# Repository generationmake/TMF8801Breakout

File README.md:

# TMF8801Breakout
Breakout board for the ams TMF8801 1D time-of-flight sensor

## Pinout

### CN1 and CN2

This is a regular 0.1-inch pin header.

| pin number | signal on CN1 | signal on CN2|
|:----------:|:-------------:|:------------:|
| 1          | VCC           | VCC          |
| 2          | GND           | GND          |
| 3          | I2C_SDA       | I2C_SDA      |
| 4          | I2C_SCL       | I2C_SCL      |
| 5          | INT           | INT          |
| 6          | ENABLE        | GPIO0        |
| 7          | not available | GPIO1        |

Several TMF8801Breakout boards can be used by connecting CN1 to CN2 of the previous board. GPIO0 is used to enabled the following TMF8801 and thus giving the possibility to change the I2C address of each device one after another.

### CN3 and CN4

This is Arduino ESLOV connector. JST SH 1mm 5-pin.

| pin number | signal on CN3 | signal on CN4|
|:----------:|:-------------:|:------------:|
| 1          | VCC           | VCC          |
| 2          | GND           | GND          |
| 3          | I2C_SDA       | I2C_SDA      |
| 4          | I2C_SCL       | I2C_SCL      |
| 5          | ENABLE        | GPIO0        |

Several TMF8801Breakout boards can be used by connecting CN3 to CN4 of the previous board. GPIO0 is used to enabled the following TMF8801 and thus giving the possibility to change the I2C address of each device one after another.

This connector does not allow the use of interrupts.

## PCB

### Top

### Bottom

## Resources

### Datasheets

 * https://ams.com/documents/20143/36005/TMF8801_DS000648_5-01.pdf

### Arduino Libraries

* [107-Arduino-TMF8801](https://github.com/107-systems/107-Arduino-TMF8801)

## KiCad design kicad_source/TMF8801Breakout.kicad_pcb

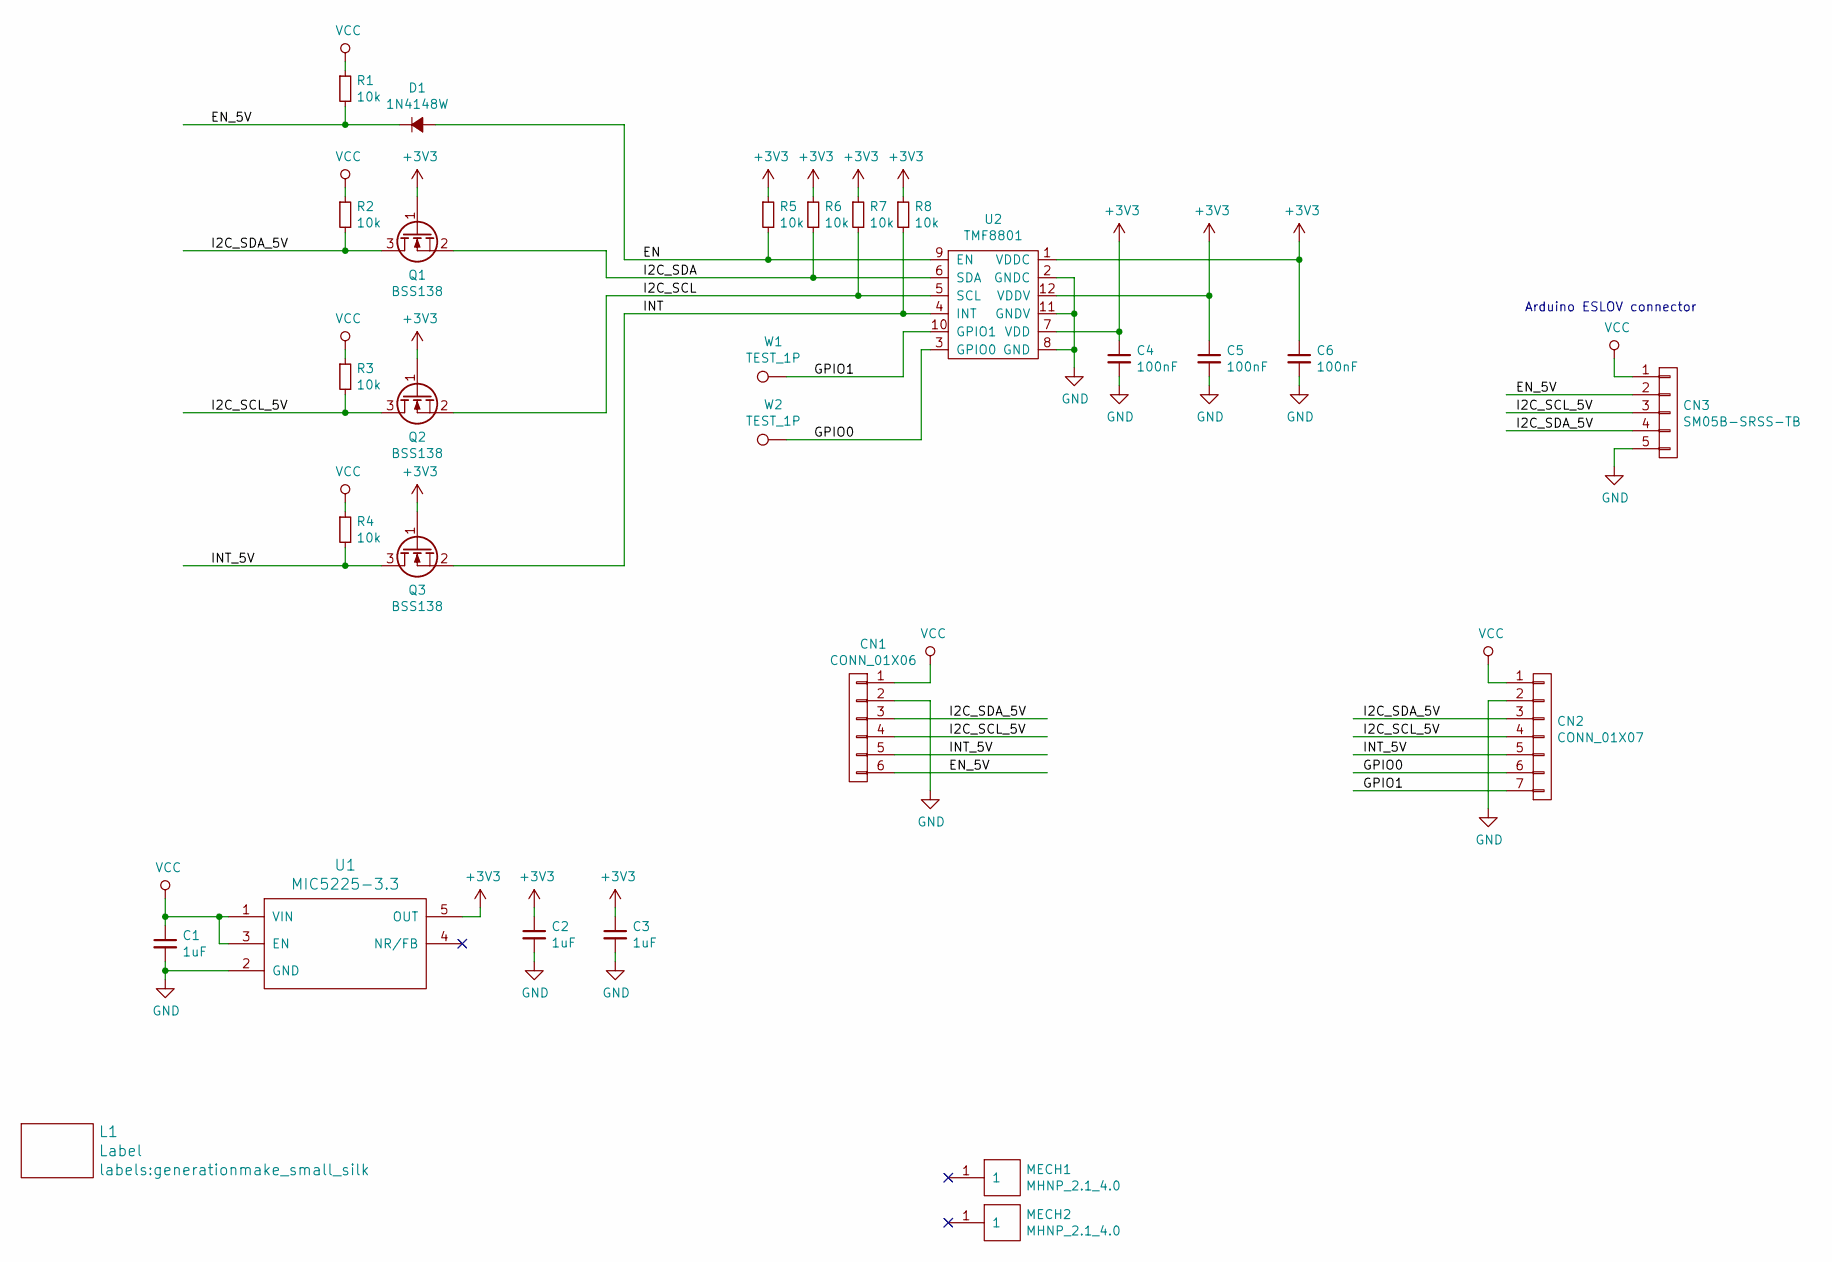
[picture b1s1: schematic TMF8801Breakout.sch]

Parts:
C1, C2, C3: 1uF; C_0603
C4, C5, C6: 100nF; C_0603
CN1: CONN_01X06; Pin_Header_Straight_1x06
CN2: CONN_01X07; Pin_Header_Straight_1x07
CN3: SM05B-SRSS-TB; JST_SH_SM05B-SRSS-TB_1x05-1MP_P1.00mm_Horizontal
D1: 1N4148W; SOD-123
L1: Label; generationmake_small_silk
MECH1, MECH2: MHNP_2.1_4.0; MH_210_400_NP
Q1, Q2, Q3: BSS138; SOT-23
R1, R2, R3, R4, R5, R6, R7, R8: 10k; R_0603
U1: MIC5225-3.3; SOT-23-5
U2: TMF8801
W1, W2: TEST_1P; SolderWirePad_single_1mmSMD

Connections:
+3V3: C2.1, C3.1, C4.1, C5.1, C6.1, Q1.1 (G), Q2.1 (G), Q3.1 (G), R5.1, R6.1, R7.1, R8.1, U1.5 (OUT), U2.1 (VDDC), U2.7 (VDD), U2.12 (VDDV)
/EN: D1.2 (A), R5.2, U2.9 (EN)
/EN_5V: CN1.6, CN3.2, D1.1 (K), R1.2
/GPIO0: CN2.6, U2.3 (GPIO0), W2.1
/GPIO1: CN2.7, U2.10 (GPIO1), W1.1
/I2C_SCL: Q2.2 (S), R7.2, U2.5 (SCL)
/I2C_SCL_5V: CN1.4, CN2.4, CN3.3, Q2.3 (D), R3.2
/I2C_SDA: Q1.2 (S), R6.2, U2.6 (SDA)
/I2C_SDA_5V: CN1.3, CN2.3, CN3.4, Q1.3 (D), R2.2
/INT: Q3.2 (S), R8.2, U2.4 (INT)
/INT_5V: CN1.5, CN2.5, Q3.3 (D), R4.2
GND: C1.2, C2.2, C3.2, C4.2, C5.2, C6.2, CN1.2, CN2.2, CN3.5, U1.2 (GND), U2.2 (GNDC), U2.8 (GND), U2.11 (GNDV)
VCC: C1.1, CN1.1, CN2.1, CN3.1, R1.1, R2.1, R3.1, R4.1, U1.1 (VIN), U1.3 (EN)

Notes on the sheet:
Arduino ESLOV connector

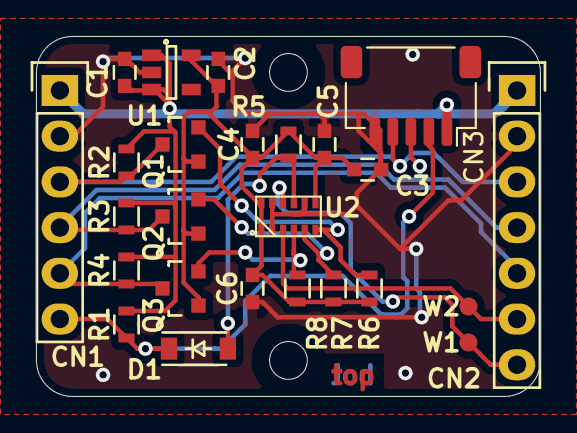
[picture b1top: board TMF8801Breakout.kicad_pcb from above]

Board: 2 copper layers, 28.0 x 20.0 mm, 28 parts (1 on the bottom side), 13 nets.

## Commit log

2020-11-24 added kicad project
2020-11-25 added layout
2020-11-25 added images, added pdf schematic
2020-11-25 added Arduino ESLOV connector
2020-11-25 moved CN1 and CN1 into 0.1 inch grid, made pcb slightly smaller, performed DRC
2020-11-25 updated images
2020-11-27 added second ESLOV connector
